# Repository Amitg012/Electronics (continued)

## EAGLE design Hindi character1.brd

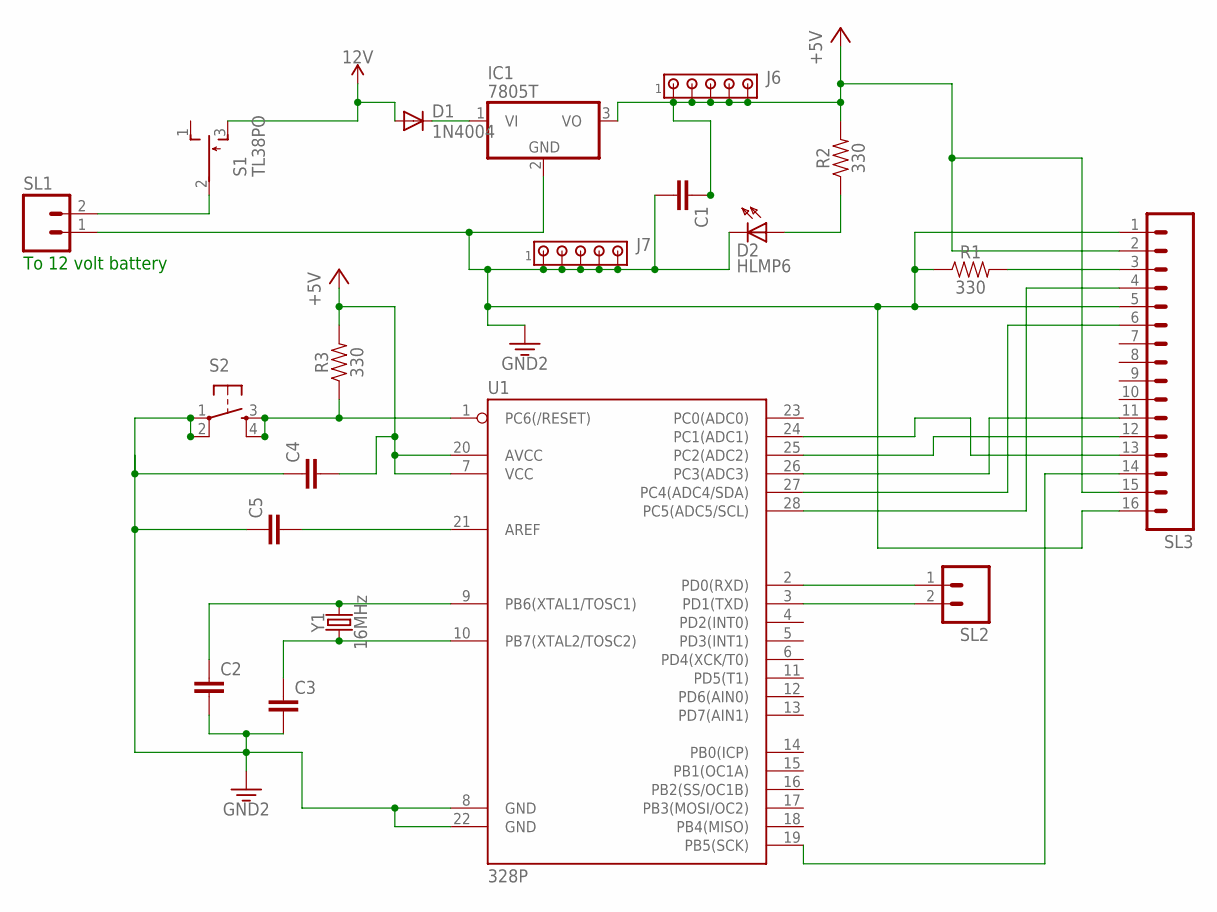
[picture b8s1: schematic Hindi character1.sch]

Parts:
C1, C2, C3, C4, C5: C5/2.5; C5B2.5
D1: 1N4004; DO41-10
D2: HLMP6
IC1: 7805T; TO220H
J6, J7: MTA05-100; 10X05MTA
R1, R2, R3: 330; AXIAL-0.3
S1: TL38PO; TL3XPO
S2: TAC_SWITCHPTH; TACTILE-PTH
SL1, SL2: MA02; 02PA
SL3: MA16; 16PA
U1: 328P; DIP28
Y1: 16MHz; HC49US

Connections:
3.3V: C1.2, C2.2, C3.2, C4.1, C5.1, D2.K, IC1.2 (GND), J7.1, J7.2, J7.3, J7.4, J7.5, R1.P$1 (1), S2.1, S2.2, SL1.1, SL3.1, SL3.5, SL3.16, U1.8 (GND), U1.22 (GND)
12V: D1.A, S1.3 (S)
+5V: C1.1, C4.2, IC1.3 (VO), J6.1, J6.2, J6.3, J6.4, J6.5, R2.P$2 (2), R3.P$2 (2), SL3.2, SL3.15, U1.7 (VCC), U1.20 (AVCC)
unnamed: SL2.1, U1.2 (PD0(RXD))
unnamed: SL2.2, U1.3 (PD1(TXD))
unnamed: SL3.4, U1.28 (PC5(ADC5/SCL))
unnamed: SL3.6, U1.27 (PC4(ADC4/SDA))
unnamed: R1.P$2 (2), SL3.3
unnamed: SL3.11, U1.26 (PC3(ADC3))
unnamed: D2.A, R2.P$1 (1)
unnamed: C3.1, U1.10 (PB7(XTAL2/TOSC2)), Y1.1
unnamed: SL3.12, U1.25 (PC2(ADC2))
unnamed: R3.P$1 (1), S2.3, S2.4, U1.1 (PC6(/RESET))
unnamed: SL3.13, U1.24 (PC1(ADC1))
unnamed: C5.2, U1.21 (AREF)
unnamed: SL3.14, U1.19 (PB5(SCK))
unnamed: S1.2, SL1.2
unnamed: D1.C, IC1.1 (VI)
unnamed: C2.1, U1.9 (PB6(XTAL1/TOSC1)), Y1.2

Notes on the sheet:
To 12 volt battery

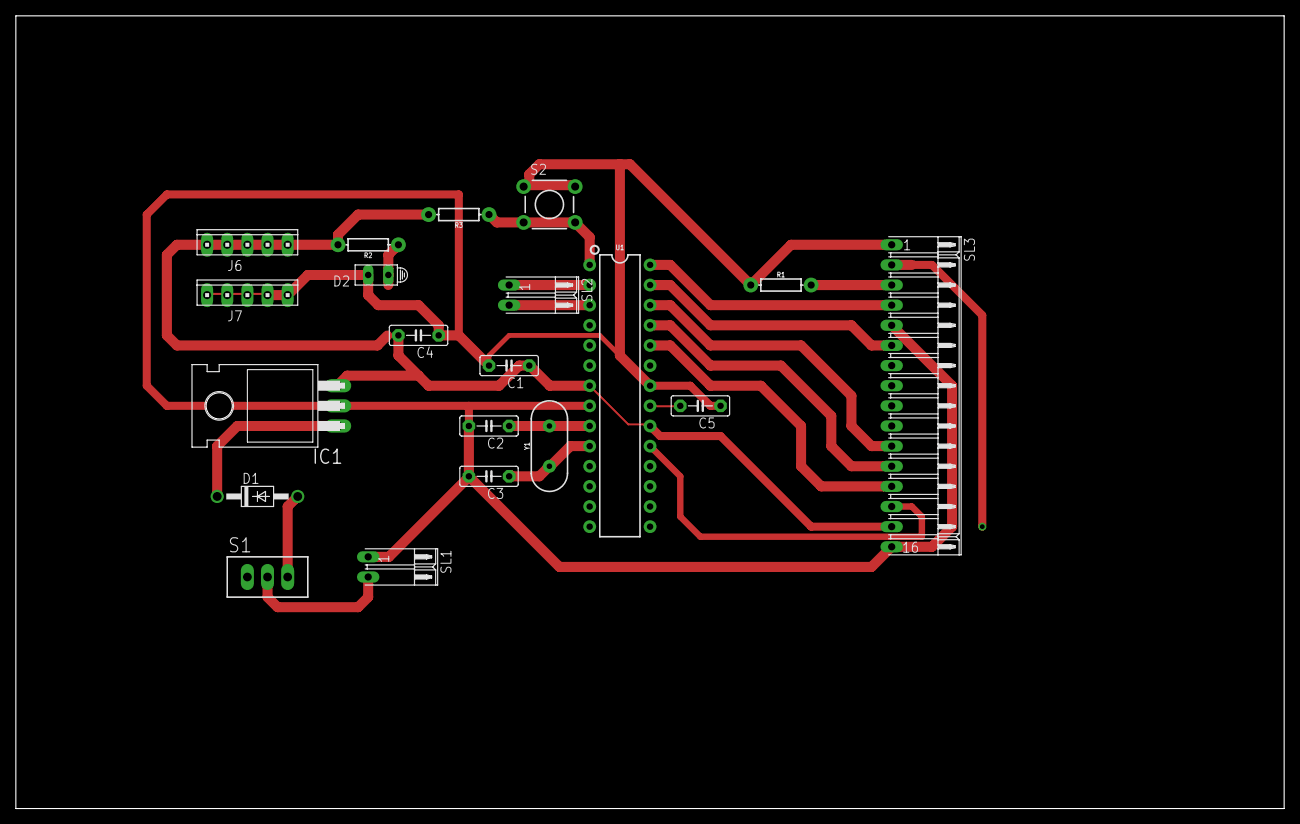
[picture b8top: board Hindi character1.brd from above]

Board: 2 copper layers, 160.0 x 100.0 mm, 20 parts (0 on the bottom side), 19 nets.

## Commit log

2021-09-02 Completed
